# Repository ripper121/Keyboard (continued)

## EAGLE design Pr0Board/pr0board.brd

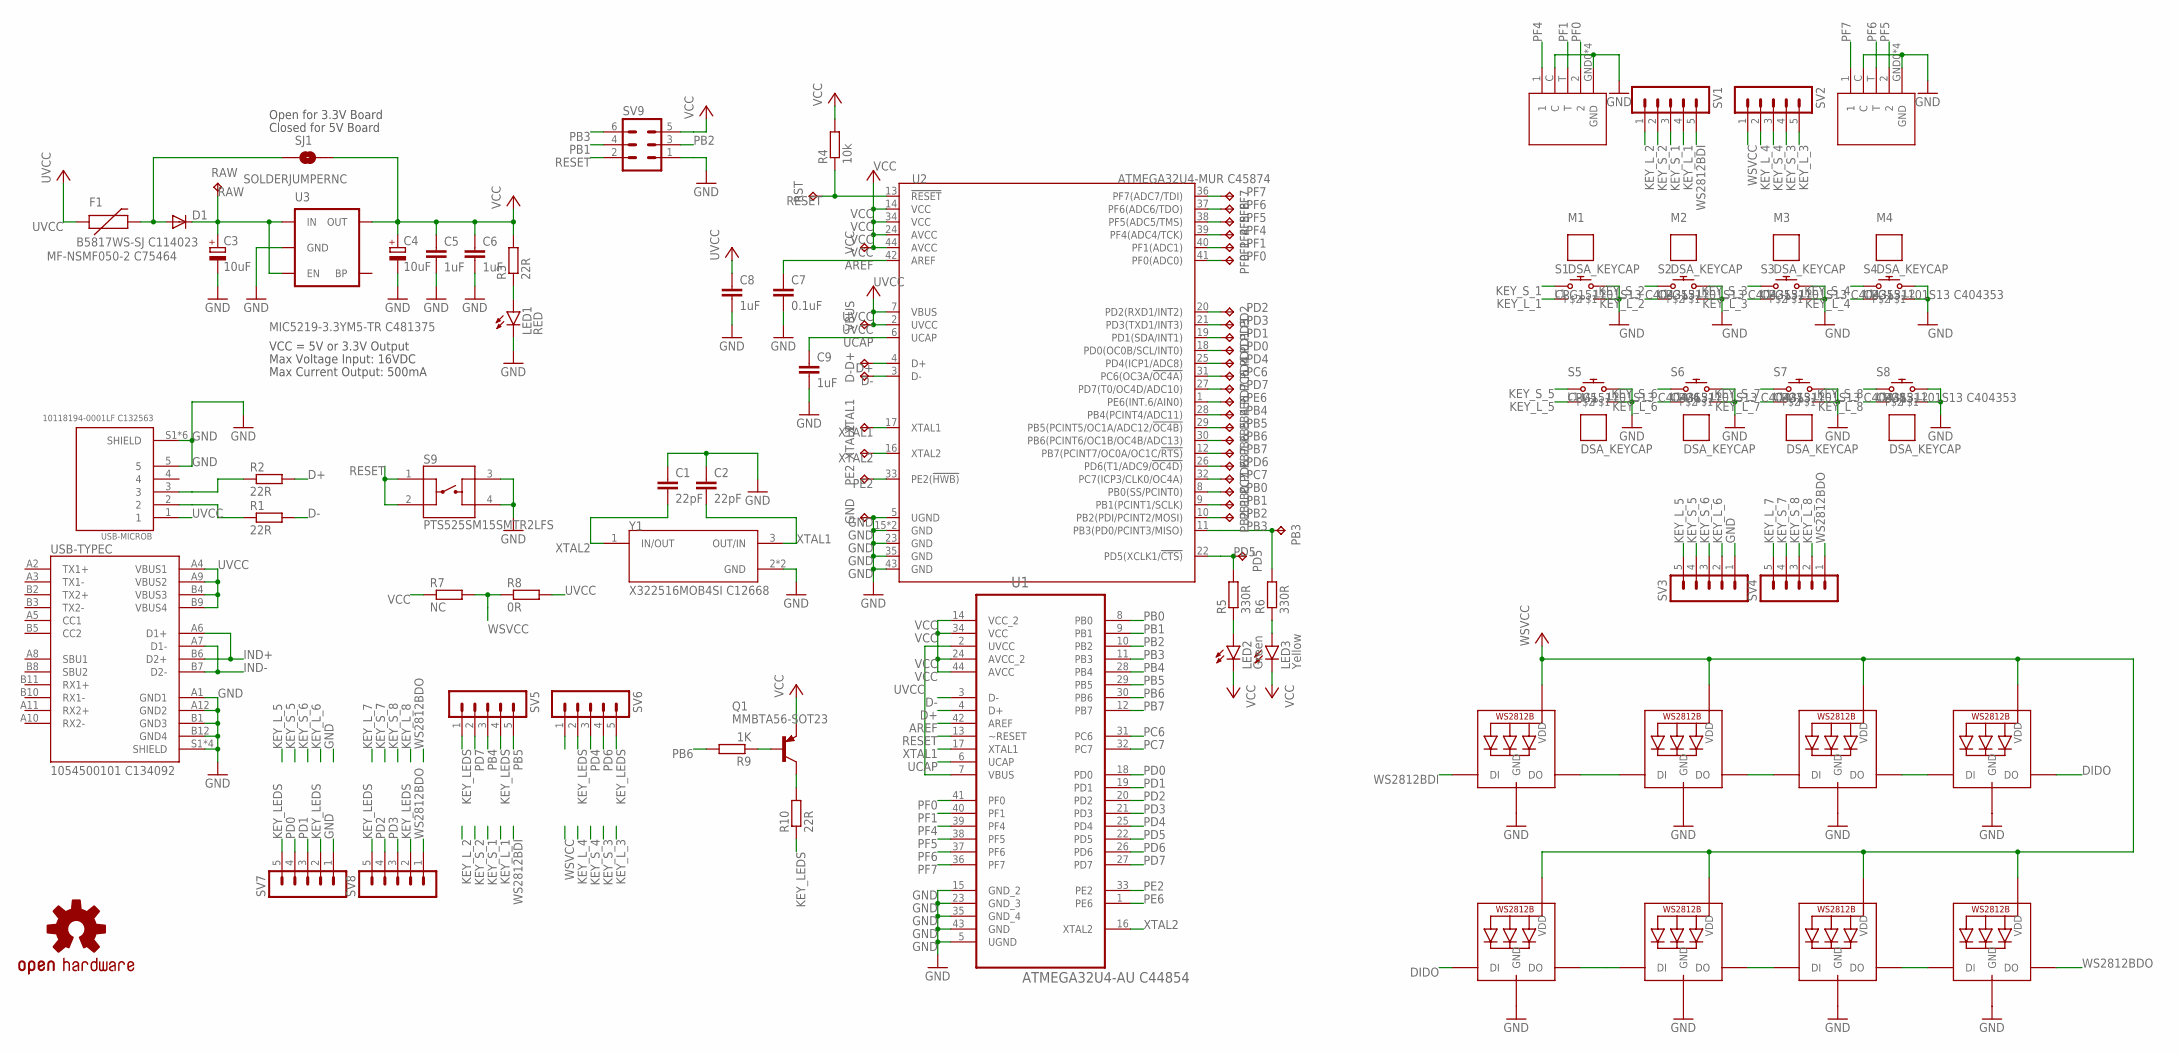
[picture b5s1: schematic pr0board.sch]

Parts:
C1, C2: 22pF; C0603
C3, C4: 10uF; CT3216
C5, C6, C8, C9: 1uF; C0603
C7: 0.1uF; C0603
D1: B5817WS-SJ C114023; SOD-323
D+: TPB1,27; B1,27
D-: TPB1,27; B1,27
F1: MF-NSMF050-2 C75464; PTC-1206
GND: TPB1,27; B1,27
LED1: RED; CHIP-LED0603
LED2: Green; CHIP-LED0603
LED3: Yellow; CHIP-LED0603
LED4, LED5, LED6, LED7, LED8, LED9, LED10, LED11: WS2812B3535; LED3535
M1, M2, M3, M4, M5, M6, M7, M8: DSA_KEYCAP
PB0, PB1, PB2, PB3, PB4, PB5, PB6, PB7: TPB1,27; B1,27
PC6, PC7: TPB1,27; B1,27
PD0, PD1, PD2, PD3, PD4, PD5, PD6, PD7: TPB1,27; B1,27
PE2, PE6: TPB1,27; B1,27
PF0, PF1, PF4, PF5, PF6, PF7: TPB1,27; B1,27
Q1: MMBTA56-SOT23; SOT23
R1, R2, R3: 22R; R0603
R4: 10k; R0603
R5, R6: 330R; R0603
R7: NC; R0603
R8: 0R; R0603
R9: 1K; R0603
R10: 22R; R0805
RAW: TPB1,27; B1,27
RST: TPB1,27; B1,27
S1, S2, S3, S4, S5, S6, S7, S8: CPG151101S13 C404353; CHERRY_MX_LED
S9: PTS525SM15SMTR2LFS; SW_PTS525SM15SMTR2LFS
SJ1: SOLDERJUMPERNC; SJ_2S
SV1, SV2, SV3, SV4, SV5, SV6, SV7, SV8: MA05-1
SV9: MA03-2
U1: ATMEGA32U4-AU C44854; QFP80P1200X1200X120-44N
U2: ATMEGA32U4-MUR C45874; QFN44G-0.5-7X7MM
U3: MIC5219-3.3YM5-TR C481375; SC70
U$1: OSHW-LOGOS; OSHW-LOGO-S
U$2, U$3: TM-2024A
USB-MICROB: 10118194-0001LF C132563; AMPHENOL_10118194-0001LF
USB-TYPEC: 1054500101 C134092; MOLEX_105450-0101
VBUS: TPB1,27; B1,27
VCC: TPB1,27; B1,27
XTAL1, XTAL2: TPB1,27; B1,27
Y1: X322516MOB4SI C12668; XTAL_ECS-160-18-33Q-DS

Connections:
AREF: C7.1, U1.42 (AREF), U2.42 (AREF)
D+: D+.TP, R2.2, U1.4 (D+), U2.4 (D+)
D-: D-.TP, R1.2, U1.3 (D-), U2.3 (D-)
DIDO: LED7.3 (DO), LED8.1 (DI)
GND: C1.1, C2.1, C3.-, C4.-, C5.2, C6.2, C7.2, C8.2, C9.2, GND.TP, LED1.C, LED4.4 (GND), LED5.4 (GND), LED6.4 (GND), LED7.4 (GND), LED8.4 (GND), LED9.4 (GND), LED10.4 (GND), LED11.4 (GND), S1.L2, S1.S2 (2), S2.L2, S2.S2 (2), S3.L2, S3.S2 (2), S4.L2, S4.S2 (2), S5.L2, S5.S2 (2), S6.L2, S6.S2 (2), S7.L2, S7.S2 (2), S8.L2, S8.S2 (2), S9.3, S9.4, SV3.1, SV7.1, SV9.1, U1.5 (UGND), U1.15 (GND_2), U1.23 (GND_3), U1.35 (GND_4), U1.43 (GND), U2.5 (UGND), U2.15 (GND), U2.23 (GND), U2.35 (GND), U2.43 (GND), U2.TAB (GND), U3.2 (GND), U$2.C, U$2.GND0 (GND), U$2.GND1 (GND), U$2.GND2 (GND), U$2.GND3 (GND), U$3.C, U$3.GND0 (GND), U$3.GND1 (GND), U$3.GND2 (GND), U$3.GND3 (GND), USB-MICROB.5, USB-MICROB.S1 (SHIELD), USB-MICROB.S2 (SHIELD), USB-MICROB.S3 (SHIELD), USB-MICROB.S4 (SHIELD), USB-MICROB.S5 (SHIELD), USB-MICROB.S6 (SHIELD), USB-TYPEC.A1 (GND1), USB-TYPEC.A12 (GND2), USB-TYPEC.B1 (GND3), USB-TYPEC.B12 (GND4), USB-TYPEC.S1 (SHIELD), USB-TYPEC.S2 (SHIELD), USB-TYPEC.S3 (SHIELD), USB-TYPEC.S4 (SHIELD), Y1.2 (GND), Y1.4 (GND)
IND+: R2.1, USB-MICROB.3, USB-TYPEC.A6 (D1+), USB-TYPEC.B6 (D2+)
IND-: R1.1, USB-MICROB.2, USB-TYPEC.A7 (D1-), USB-TYPEC.B7 (D2-)
KEY_LEDS: R10.1, SV5.1, SV5.4, SV6.2, SV6.5, SV7.2, SV7.5, SV8.2, SV8.5
KEY_L_1: S1.L1, SV1.4
KEY_L_2: S2.L1, SV1.1
KEY_L_3: S3.L1, SV2.5
KEY_L_4: S4.L1, SV2.2
KEY_L_5: S5.L1, SV3.5
KEY_L_6: S6.L1, SV3.2
KEY_L_7: S7.L1, SV4.5
KEY_L_8: S8.L1, SV4.2
KEY_S_1: S1.S1 (1), SV1.3
KEY_S_2: S2.S1 (1), SV1.2
KEY_S_3: S3.S1 (1), SV2.4
KEY_S_4: S4.S1 (1), SV2.3
KEY_S_5: S5.S1 (1), SV3.4
KEY_S_6: S6.S1 (1), SV3.3
KEY_S_7: S7.S1 (1), SV4.4
KEY_S_8: S8.S1 (1), SV4.3
unnamed: D1.2 (A), F1.2, SJ1.1
unnamed: LED1.A, R3.1
unnamed: LED3.A, R6.1
unnamed: LED2.A, R5.1
unnamed: Q1.1 (B), R9.1
unnamed: LED4.3 (DO), LED5.1 (DI)
unnamed: LED5.3 (DO), LED6.1 (DI)
unnamed: LED6.3 (DO), LED7.1 (DI)
unnamed: Q1.3 (C), R10.2
unnamed: LED8.3 (DO), LED9.1 (DI)
unnamed: LED9.3 (DO), LED10.1 (DI)
unnamed: LED10.3 (DO), LED11.1 (DI)
PB0: PB0.TP, U1.8 (PB0), U2.8 (PB0(SS/PCINT0))
PB1: PB1.TP, SV9.4, U1.9 (PB1), U2.9 (PB1(PCINT1/SCLK))
PB2: PB2.TP, SV9.3, U1.10 (PB2), U2.10 (PB2(PDI/PCINT2/MOSI))
PB3: PB3.TP, R6.2, SV9.6, U1.11 (PB3), U2.11 (PB3(PD0/PCINT3/MISO))
PB4: PB4.TP, SV5.3, U1.28 (PB4), U2.28 (PB4(PCINT4/ADC11))
PB5: PB5.TP, SV5.5, U1.29 (PB5), U2.29 (PB5(PCINT5/OC1A/ADC12/!OC4B))
PB6: PB6.TP, R9.2, U1.30 (PB6), U2.30 (PB6(PCINT6/OC1B/OC4B/ADC13))
PB7: PB7.TP, U1.12 (PB7), U2.12 (PB7(PCINT7/OC0A/OC1C/!RTS))
PC6: PC6.TP, U1.31 (PC6), U2.31 (PC6(OC3A/!OC4A))
PC7: PC7.TP, U1.32 (PC7), U2.32 (PC7(ICP3/CLK0/OC4A))
PD0: PD0.TP, SV7.4, U1.18 (PD0), U2.18 (PD0(OC0B/SCL/INT0))
PD1: PD1.TP, SV7.3, U1.19 (PD1), U2.19 (PD1(SDA/INT1))
PD2: PD2.TP, SV8.4, U1.20 (PD2), U2.20 (PD2(RXD1/INT2))
PD3: PD3.TP, SV8.3, U1.21 (PD3), U2.21 (PD3(TXD1/INT3))
PD4: PD4.TP, SV6.3, U1.25 (PD4), U2.25 (PD4(ICP1/ADC8))
PD5: PD5.TP, R5.2, U1.22 (PD5), U2.22 (PD5(XCLK1/!CTS))
PD6: PD6.TP, SV6.4, U1.26 (PD6), U2.26 (PD6(T1/ADC9/!OC4D))
PD7: PD7.TP, SV5.2, U1.27 (PD7), U2.27 (PD7(T0/OC4D/ADC10))
PE2: PE2.TP, U1.33 (PE2), U2.33 (PE2(!HWB))
PE6: PE6.TP, U1.1 (PE6), U2.1 (PE6(INT.6/AIN0))
PF0: PF0.TP, U1.41 (PF0), U2.41 (PF0(ADC0)), U$2.2
PF1: PF1.TP, U1.40 (PF1), U2.40 (PF1(ADC1)), U$2.T
PF4: PF4.TP, U1.39 (PF4), U2.39 (PF4(ADC4/TCK)), U$2.1
PF5: PF5.TP, U1.38 (PF5), U2.38 (PF5(ADC5/TMS)), U$3.2
PF6: PF6.TP, U1.37 (PF6), U2.37 (PF6(ADC6/TDO)), U$3.T
PF7: PF7.TP, U1.36 (PF7), U2.36 (PF7(ADC7/TDI)), U$3.1
RAW: C3.+, D1.1 (C), RAW.TP, U3.1 (IN), U3.3 (EN)
RESET: R4.1, RST.TP, S9.1, S9.2, SV9.2, U1.13 (~RESET), U2.13 (!RESET)
UCAP: C9.1, U1.6 (UCAP), U2.6 (UCAP)
UVCC: C8.1, F1.1, R8.2, U1.2 (UVCC), U1.7 (VBUS), U2.2 (UVCC), U2.7 (VBUS), USB-MICROB.1, USB-TYPEC.A4 (VBUS1), USB-TYPEC.A9 (VBUS2), USB-TYPEC.B4 (VBUS3), USB-TYPEC.B9 (VBUS4), VBUS.TP
VCC: C4.+, C5.1, C6.1, LED2.C, LED3.C, Q1.2 (E), R3.2, R4.2, R7.1, SJ1.2, SV9.5, U1.14 (VCC_2), U1.24 (AVCC_2), U1.34 (VCC), U1.44 (AVCC), U2.14 (VCC), U2.24 (AVCC), U2.34 (VCC), U2.44 (AVCC), U3.5 (OUT), VCC.TP
WS2812BDI: LED4.1 (DI), SV1.5
WS2812BDO: LED11.3 (DO), SV4.1, SV8.1
WSVCC: LED4.2 (VDD), LED5.2 (VDD), LED6.2 (VDD), LED7.2 (VDD), LED8.2 (VDD), LED9.2 (VDD), LED10.2 (VDD), LED11.2 (VDD), R7.2, R8.1, SV2.1, SV6.1
XTAL1: C2.2, U1.17 (XTAL1), U2.17 (XTAL1), XTAL1.TP, Y1.3 (OUT/IN)
XTAL2: C1.2, U1.16 (XTAL2), U2.16 (XTAL2), XTAL2.TP, Y1.1 (IN/OUT)

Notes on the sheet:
Max Voltage Input: 16VDC
Max Current Output: 500mA
VCC = 5V or 3.3V Output
Open for 3.3V Board
Closed for 5V Board

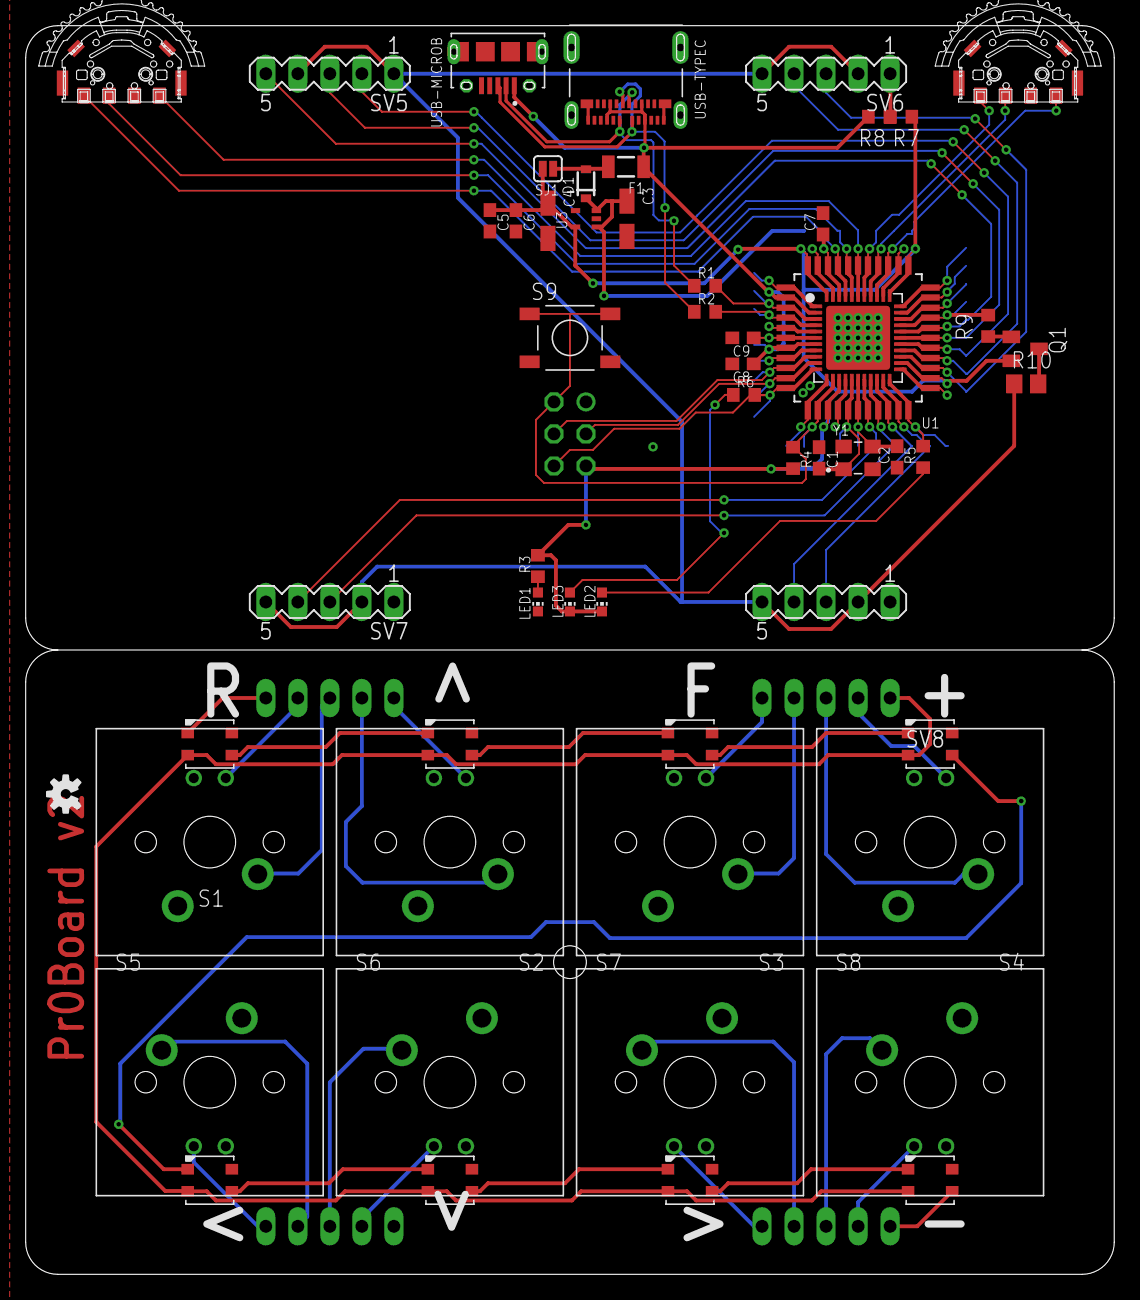
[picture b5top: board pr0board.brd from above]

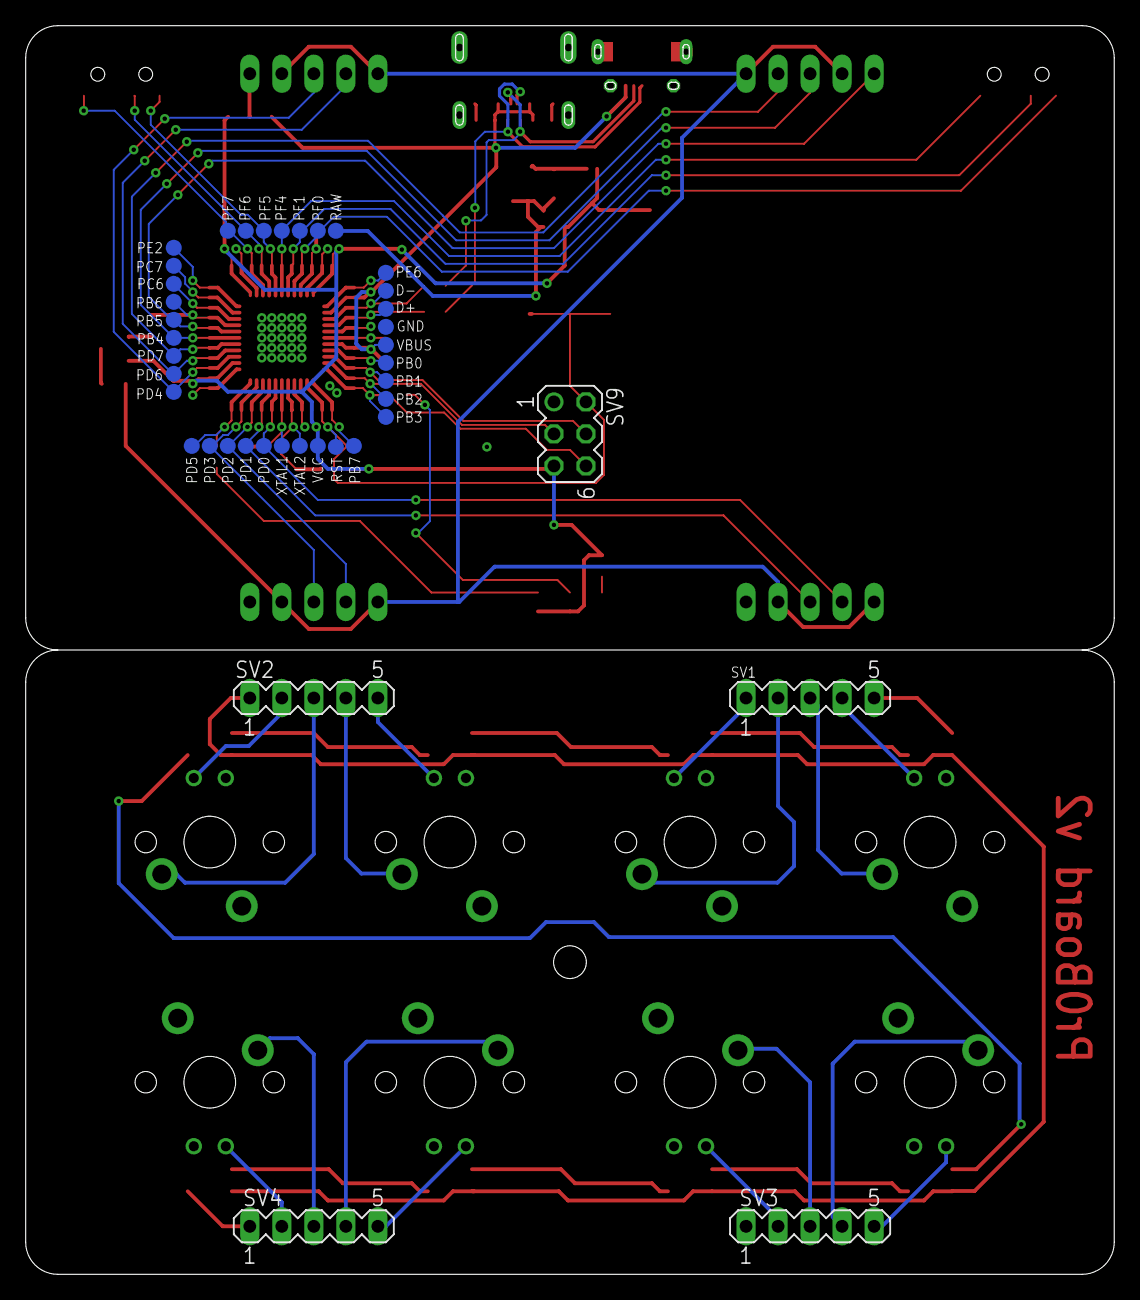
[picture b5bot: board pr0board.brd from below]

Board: 2 copper layers, 86.4 x 99.1 mm, 104 parts (40 on the bottom side), 72 nets.

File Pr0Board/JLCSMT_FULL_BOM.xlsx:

Comment | Designator | Footprint | LCSC Part #（optional）
Pin Header | SV1, SV2, SV3, SV4, SV5, SV6, SV7, SV8 | MA05-1 | C390676
0.1uF | C7 | C0603 | C497032
0Ω | R8 | R0603 | C177335
10KΩ | R4 | R0603 | C15401
10uF | C3, C4 | CT3216 | C128256 |  |  |  |  |  | 100uF
1KΩ | R9 | R0603 | C25585 |  |  |  |  |  | 100nF
1uF | C5, C6, C8, C9 | C0603 | C26413 |  |  |  |  |  | 10uF
22Ω | R1, R2, R3 | R0603 | C177338 |  |  |  |  |  | 15KΩ
22Ω | R10 | R0805 | C25295
22pF | C1, C2 | C0603 | C525244
330Ω | R5, R6 | R0603 | C177341
ATMEGA32U4-AU | U1 | QFP80P1200X1200X120-44N | C44854
B5817WS-SJ | D1 | SOD-323 | C114023
CPG151101S13 | S1, S2, S3, S4, S5, S6, S7, S8 | CHERRY_MX_LED | C404353
MF-NSMF050-2 | F1 | PTC-1206 | C75464
MIC5219-3.3YM5-TR | U3 | SC70 | C481375
PMBT3906,215 | Q1 | SOT23 | C8670
PTS525SM15SMTR2LFS | S9 | SW_PTS525SM15SMTR2LFS | C318884
TM-2024A | U$2, U$3 | TM-2024A | C561480
WS2812B-Mini | LED4, LED5, LED6, LED7, LED8, LED9, LED10, LED11 | LED3535 | C527089
X322516MOB4SI | Y1 | XTAL_ECS-160-18-33Q-DS | C12668
Yellow | LED3 | CHIP-LED0603 | C375445
Green | LED2 | CHIP-LED0603 | C205443
RED | LED1 | CHIP-LED0603 | C118330
10118194-0001LF | USB-MICROB | AMPHENOL_10118194-0001LF | C132563
1054500101 | USB-TYPEC | MOLEX_105450-0101 | C134092

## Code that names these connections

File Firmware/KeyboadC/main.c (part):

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
/* ----------------------- hardware I/O abstraction ------------------------ */

#define LED1                PC0
#define LED1_PORT           PORTC
#define LED1_DDR            DDRC
#define LED1_PIN            PINC

#define LED2                PC1
#define LED2_PORT           PORTC
#define LED2_DDR            DDRC
#define LED2_PIN            PINC

#define COL1                PC2
#define COL1_PORT           PORTC
#define COL1_DDR            DDRC
#define COL1_PIN            PINC

#define COL2                PC3
#define COL2_PORT           PORTC
#define COL2_DDR            DDRC
#define COL2_PIN            PINC

#define COL3                PC4
#define COL3_PORT           PORTC
#define COL3_DDR            DDRC
#define COL3_PIN            PINC

#define COL4                PC5
#define COL4_PORT           PORTC
#define COL4_DDR            DDRC
#define COL4_PIN            PINC

#define ROW1                PD0
#define ROW1_PORT           PORTD
#define ROW1_DDR            DDRD
#define ROW1_PIN            PIND

#define ROW2                PD1
#define ROW2_PORT           PORTD
#define ROW2_DDR            DDRD
#define ROW2_PIN            PIND

static void resetMatrix(void)
{
	//Key Matrix
	//COLS
	pinIN(COL1);//Input
	pullUpOff(COL1);//Low
	pinIN(COL2);//Input
	pullUpOff(COL2);//Low
	pinIN(COL3);//Input
	pullUpOff(COL3);//Low
	pinIN(COL4);//Input
	pullUpOff(COL4);//Low
	//ROWS
	pinIN(ROW1);//Input
	pullUpOff(ROW1);//Low
	pinIN(ROW2);//Input
	pullUpOff(ROW2);//Low
}

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{
	//Volume Keys
	resetMatrix();
	pinOUT(ROW1);
	set_high(ROW1);
	pinOUT(ROW2);
	set_low(ROW2);

	pinIN(COL1);
	pullUpOn(COL1);
	pinIN(COL3);
	pullUpOn(COL3);
	pinIN(COL4);
	pullUpOn(COL4);
	_delay_ms(1);
	
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	
	//ROW1 & COLS
	resetMatrix();
	pinOUT(ROW1);
	set_low(ROW1);
	pinOUT(ROW2);
	set_high(ROW2);
	
	pinIN(COL1);
	pullUpOn(COL1);
	pinIN(COL2);
	pullUpOn(COL2);
	pinIN(COL3);
	pullUpOn(COL3);
	pinIN(COL4);
	pullUpOn(COL4);
	_delay_ms(1);
	
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	
	//ROW2 & COLS
	resetMatrix();
	pinOUT(ROW1);
	set_high(ROW1);
	pinOUT(ROW2);
	set_low(ROW2);

	pinIN(COL1);
	pullUpOn(COL1);
	pinIN(COL2);
	pullUpOn(COL2);
	pinIN(COL3);
	pullUpOn(COL3);
	pinIN(COL4);
	pullUpOn(COL4);
	_delay_ms(1);
	
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
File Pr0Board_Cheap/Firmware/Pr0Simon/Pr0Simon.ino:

#include <Adafruit_NeoPixel.h>
#ifdef __AVR__
#include <avr/power.h>
#endif


#define LEDYELLOW   0
#define LEDGREEN    1
#define KEY_S_2     2
#define KEY_S_1     3
#define S11         4
#define ST1         5
#define S21         6
#define KEY_S_5     7
#define KEY_S_6     8
#define LEDPWM      9
#define WS2812BDI   10
#define S12         MOSI
#define ST2         MISO
#define S22         SCK
#define KEY_S_7     A0
#define KEY_S_8     A1
#define KEY_S_4     A2
#define KEY_S_3     A3
#define DEBOUNCE    50

Adafruit_NeoPixel ws2812b = Adafruit_NeoPixel(8, WS2812BDI, NEO_GRB + NEO_KHZ800);

void setup()
{
  Serial.begin(115200);
  pinMode(LEDYELLOW, OUTPUT);
  pinMode(LEDGREEN, OUTPUT);

  pinMode(KEY_S_1, INPUT_PULLUP);
  pinMode(KEY_S_2, INPUT_PULLUP);
  pinMode(KEY_S_3, INPUT_PULLUP);
  pinMode(KEY_S_4, INPUT_PULLUP);
  pinMode(KEY_S_5, INPUT_PULLUP);
  pinMode(KEY_S_6, INPUT_PULLUP);
  pinMode(KEY_S_7, INPUT_PULLUP);
  pinMode(KEY_S_8, INPUT_PULLUP);

  pinMode(S11, INPUT_PULLUP);
  pinMode(ST1, INPUT_PULLUP);
  pinMode(S21, INPUT_PULLUP);

  pinMode(S12, INPUT_PULLUP);
  pinMode(ST2, INPUT_PULLUP);
  pinMode(S22, INPUT_PULLUP);

  ws2812b.begin();
  ws2812b.setBrightness(50);
  ws2812b.show(); // Initialize all pixels to 'off'
  randomSeed(analogRead(0));

}

byte ledCounter = 0;
int colors = 0;
unsigned long previousMillis = 0;
const long interval = 1;
bool updownCount = false;
byte simonSays[1024];
int simonCount = 0;

void loop()
{
  simonSays[simonCount++] = random(4);

  //show sequence
  for (int i = 0; i < simonCount; i++) {
    ws2812b.clear();
    ws2812b.show();
    delay(600);
    if (simonSays[i] == 0) {
      ws2812b.setPixelColor(0, ws2812b.Color(255, 0, 0));
    }
    if (simonSays[i] == 1) {
      ws2812b.setPixelColor(1, ws2812b.Color(0, 0, 255));
    }
    if (simonSays[i] == 2) {
      ws2812b.setPixelColor(5, ws2812b.Color(255, 255, 0));
    }
    if (simonSays[i] == 3) {
      ws2812b.setPixelColor(4, ws2812b.Color(0, 255, 0));
    }
    ws2812b.show();
    delay(600);
  }
  ws2812b.setPixelColor(0, ws2812b.Color(255, 0, 0));
  ws2812b.setPixelColor(1, ws2812b.Color(0, 0, 255));
  ws2812b.setPixelColor(5, ws2812b.Color(255, 255, 0));
  ws2812b.setPixelColor(4, ws2812b.Color(0, 255, 0));
  ws2812b.show();

  //do sequence
  bool rightSequence = false;
  for (int i = 0; i < simonCount; i++) {
    if (getButton() == simonSays[i]) {
      rightSequence = true;
    } else {
      rightSequence = false;
      break;
    }
  }
  delay(600);
  if (rightSequence) {
    ws2812b.clear();
    ws2812b.setPixelColor(2, ws2812b.Color(0, 255, 0));
    ws2812b.setPixelColor(3, ws2812b.Color(0, 255, 0));
    ws2812b.setPixelColor(6, ws2812b.Color(0, 255, 0));
    ws2812b.setPixelColor(7, ws2812b.Color(0, 255, 0));
    ws2812b.show();
  } else {
    ws2812b.clear();
    ws2812b.setPixelColor(2, ws2812b.Color(255, 0, 0));
    ws2812b.setPixelColor(3, ws2812b.Color(255, 0, 0));
    ws2812b.setPixelColor(6, ws2812b.Color(255, 0, 0));
    ws2812b.setPixelColor(7, ws2812b.Color(255, 0, 0));
    ws2812b.show();
    simonCount = 0;
    randomSeed(millis());
  }
  delay(1000);
}

byte getButton() {
  while (true) {
    if (!digitalRead(KEY_S_1)) {
      ws2812b.setPixelColor(0, ws2812b.Color(0, 0, 0));
      ws2812b.show();
      while (!digitalRead(KEY_S_1)) {delay(20);}
      ws2812b.setPixelColor(0, ws2812b.Color(255, 0, 0));
      ws2812b.show();
      return 0;
    }
    if (!digitalRead(KEY_S_2)) {
      ws2812b.setPixelColor(1, ws2812b.Color(0, 0, 0));
      ws2812b.show();
      while (!digitalRead(KEY_S_2)) {delay(20);}
      ws2812b.setPixelColor(1, ws2812b.Color(0, 0, 255));
      ws2812b.show();
      return 1;
    }
    if (!digitalRead(KEY_S_5)) {
      ws2812b.setPixelColor(4, ws2812b.Color(0, 0, 0));
      ws2812b.show();
      while (!digitalRead(KEY_S_5)) {delay(20);}
      ws2812b.setPixelColor(4, ws2812b.Color(0, 255, 0));
      ws2812b.show();
      return 3;
    }
    if (!digitalRead(KEY_S_6)) {
      ws2812b.setPixelColor(5, ws2812b.Color(0, 0, 0));
      ws2812b.show();
      while (!digitalRead(KEY_S_6)) {delay(20);}
      ws2812b.setPixelColor(5, ws2812b.Color(255, 255, 0));
      ws2812b.show();
      return 2;
    }
  }
}

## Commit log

2020-10-12 latest
2020-10-15 Cleanup
2020-10-15 SimonSays, MIDI Usb
2020-10-17 swap vol up / down and audio next / prev
    swap vol down / up to map:
    left: down
    right: up
    same with audio next and prev:
    left: prev
    right: next
2021-05-19 init
2021-05-19 assembly
2021-05-19 3D Files + Render
2021-05-19 Simon Says with Score
2021-05-31 Simon brightnes setting
2021-05-31 added new Lukas Game
2021-09-08 fw & bootloader
